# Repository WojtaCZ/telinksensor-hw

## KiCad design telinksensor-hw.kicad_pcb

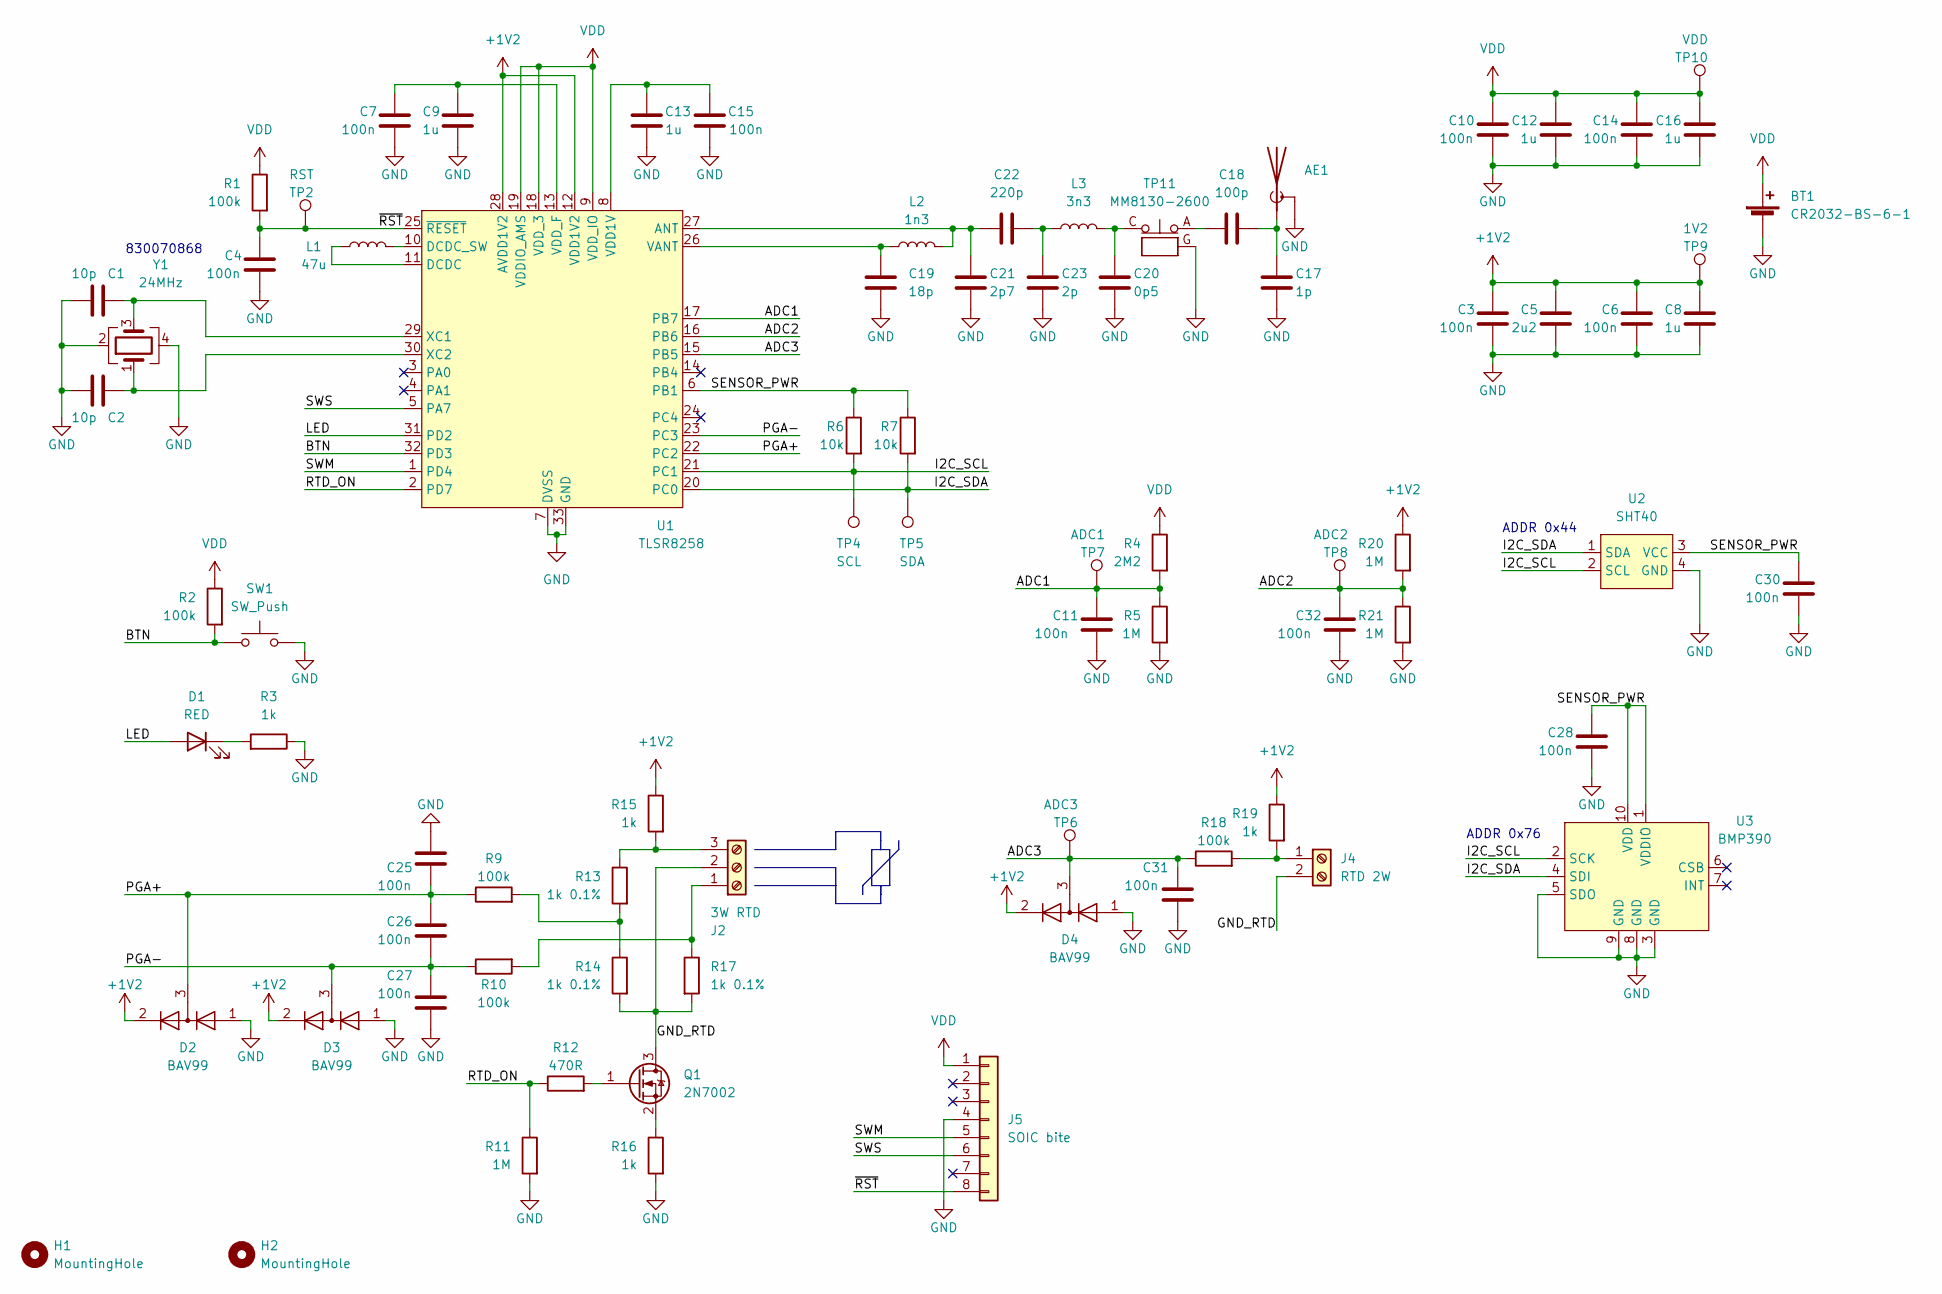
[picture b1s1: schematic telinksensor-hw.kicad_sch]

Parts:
AE1: Antenna_Shield; Texas_SWRA117D_2.4GHz_Left
BT1: CR2032-BS-6-1; BatteryHolder_Keystone_1060_1x2032
C1, C2: 10p; C_0603_1608Metric
C3, C6, C7, C10, C14, C15, C28, C30: 100n; C_0402_1005Metric
C4, C11, C25, C26, C27, C31, C32: 100n; C_0603_1608Metric
C5: 2u2; C_0402_1005Metric
C8, C9, C12, C13, C16: 1u; C_0402_1005Metric
C17: 1p; C_0402_1005Metric
C18: 100p; C_0402_1005Metric
C19: 18p; C_0402_1005Metric
C20: 0p5; C_0402_1005Metric
C21: 2p7; C_0402_1005Metric
C22: 220p; C_0402_1005Metric
C23: 2p; C_0402_1005Metric
D1: RED; LED_0603_1608Metric
D2, D3, D4: BAV99; SOT-23
H1, H2: MountingHole; MountingHole_3.2mm_M3_Pad_Via
J2: 3W RTD; TerminalBlock_bornier-3_P5.08mm
J4: RTD 2W; TerminalBlock_bornier-2_P5.08mm
J5: SOIC bite; SOIC_clipProgSmall
L1: 47u; L_0805_2012Metric
L2: 1n3; L_0402_1005Metric
L3: 3n3; L_0402_1005Metric
Q1: 2N7002; SOT-23
R1, R2, R9, R10, R18: 100k; R_0603_1608Metric
R3, R15, R16, R19: 1k; R_0603_1608Metric
R4: 2M2; R_0603_1608Metric
R5, R11, R20, R21: 1M; R_0603_1608Metric
R6, R7: 10k; R_0603_1608Metric
R12: 470R; R_0603_1608Metric
R13, R14, R17: 1k 0.1%; R_0603_1608Metric
SW1: SW_Push; SW_SPST_EVQPE1
TP2: RST; TestPoint_Pad_D1.0mm
TP4: SCL; TestPoint_Pad_D1.0mm
TP5: SDA; TestPoint_Pad_D1.0mm
TP6: ADC3; TestPoint_Pad_D1.0mm
TP7: ADC1; TestPoint_Pad_D1.0mm
TP8: ADC2; TestPoint_Pad_D1.0mm
TP9: 1V2; TestPoint_Pad_D1.0mm
TP10: VDD; TestPoint_Pad_D1.0mm
TP11: MM8130-2600
U1: TLSR8258; QFN-32-1EP_5x5mm_P0.5mm_EP3.6x3.6mm_ThermalVias
U2: SHT40
U3: BMP390
Y1: 24MHz; Crystal_SMD_3225-4Pin_3.2x2.5mm

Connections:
+1V2: C3.1, C5.1, C6.1, C8.1, D2.2 (A), D3.2 (A), D4.2 (A), R15.1, R19.1, R20.1, TP9.1, U1.12 (VDD1V2), U1.28 (AVDD1V2)
/ADC1: C11.1, R4.2, R5.1, TP7.1, U1.17 (PB7)
/ADC2: C32.1, R20.2, R21.1, TP8.1, U1.16 (PB6)
/ADC3: C31.1, D4.3 (K), R18.1, TP6.1, U1.15 (PB5)
/BTN: R2.2, SW1.2, U1.32 (PD3)
/GND_RTD: J2.2, J4.2, Q1.3 (D), R14.2, R17.2
/I2C_SCL: R6.2, TP4.1, U1.21 (PC1), U2.2 (SCL), U3.2 (SCK)
/I2C_SDA: R7.2, TP5.1, U1.20 (PC0), U2.1 (SDA), U3.4 (SDI)
/LED: D1.2 (A), U1.31 (PD2)
/PGA+: C25.2, C26.1, D2.3 (K), R9.1, U1.22 (PC2)
/PGA-: C26.2, C27.1, D3.3 (K), R10.1, U1.23 (PC3)
/RTD_ON: R11.1, R12.1, U1.2 (PD7)
/SENSOR_PWR: C28.1, C30.1, R6.1, R7.1, U1.6 (PB1), U2.3 (VCC), U3.1 (VDDIO), U3.10 (VDD)
/SWM: J5.5, U1.1 (PD4)
/SWS: J5.6, U1.5 (PA7)
/~RST: C4.1, J5.8, R1.2, TP2.1, U1.25 (~RESET)
GND: AE1.2 (Shield), BT1.2 (-), C1.2, C2.2, C3.2, C4.2, C5.2, C6.2, C7.2, C8.2, C9.2, C10.2, C11.2, C12.2, C13.2, C14.2, C15.2, C16.2, C17.2, C19.2, C20.2, C21.2, C23.2, C25.1, C27.2, C28.2, C30.2, C31.2, C32.2, D2.1 (K), D3.1 (K), D4.1 (K), J5.4, R3.1, R5.2, R11.2, R16.2, R21.2, SW1.1, TP11.G, U1.7 (DVSS), U1.33 (GND), U2.4 (GND), U3.3 (GND), U3.5 (SDO), U3.8 (GND), U3.9 (GND), Y1.2, Y1.4
unnamed: AE1.1 (A), C17.1, C18.2
unnamed: C1.1, U1.29 (XC1), Y1.3
unnamed: C2.1, U1.30 (XC2), Y1.1
unnamed: C7.1, C9.1, U1.13 (VDD_F)
unnamed: C13.1, C15.1, U1.8 (VDD1V)
unnamed: C18.1, TP11.A
unnamed: C19.1, L2.1, U1.26 (VANT)
unnamed: C20.1, L3.2, TP11.C
unnamed: C21.1, C22.1, L2.2, U1.27 (ANT)
unnamed: C22.2, C23.1, L3.1
unnamed: D1.1 (K), R3.2
unnamed: J2.1, R10.2, R17.1
unnamed: J2.3, R13.1, R15.2
unnamed: J4.1, R18.2, R19.2
unnamed: L1.1, U1.11 (DCDC)
unnamed: L1.2, U1.10 (DCDC_SW)
unnamed: Q1.1 (G), R12.2
unnamed: Q1.2 (S), R16.1
unnamed: R9.2, R13.2, R14.1
VDD: BT1.1 (+), C10.1, C12.1, C14.1, C16.1, J5.1, R1.1, R2.1, R4.1, TP10.1, U1.9 (VDD_IO), U1.18 (VDD_3), U1.19 (VDDIO_AMS)

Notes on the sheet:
ADDR 0x44
ADDR 0x76
830070868

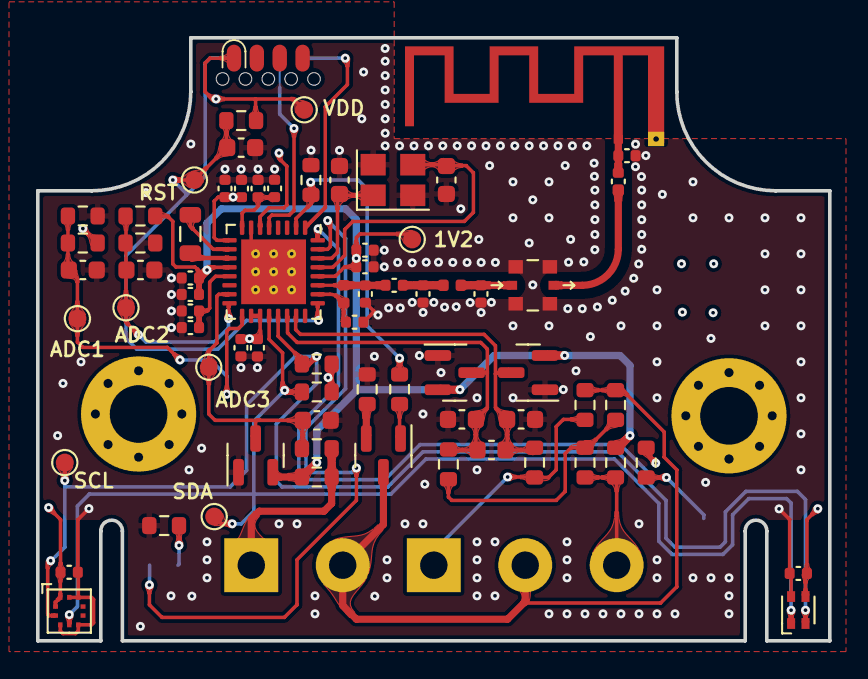
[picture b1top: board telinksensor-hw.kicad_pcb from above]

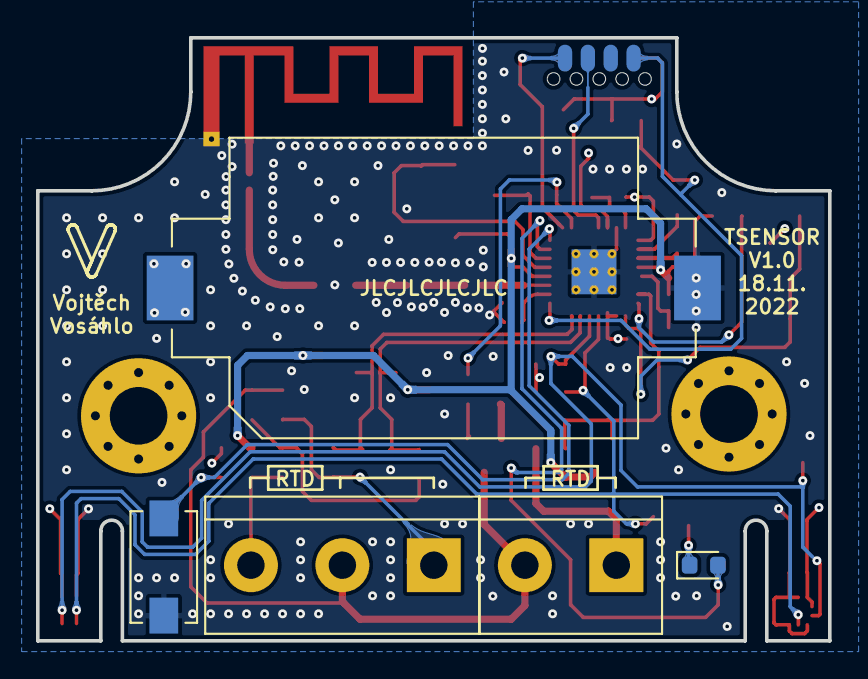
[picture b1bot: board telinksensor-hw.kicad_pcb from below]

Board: 4 copper layers, 44.0 x 33.5 mm, 79 parts (5 on the bottom side), 37 nets.

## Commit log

2022-10-02 Outline done
2022-10-04 Routing mostly done
2022-11-10 Routing almost done
2022-11-18 Routing done
2022-11-18 Added gitignore
2022-11-18 Added teardrops
2022-11-24 Finalized for production
2023-01-31 Added BOM
2023-11-26 Sync
